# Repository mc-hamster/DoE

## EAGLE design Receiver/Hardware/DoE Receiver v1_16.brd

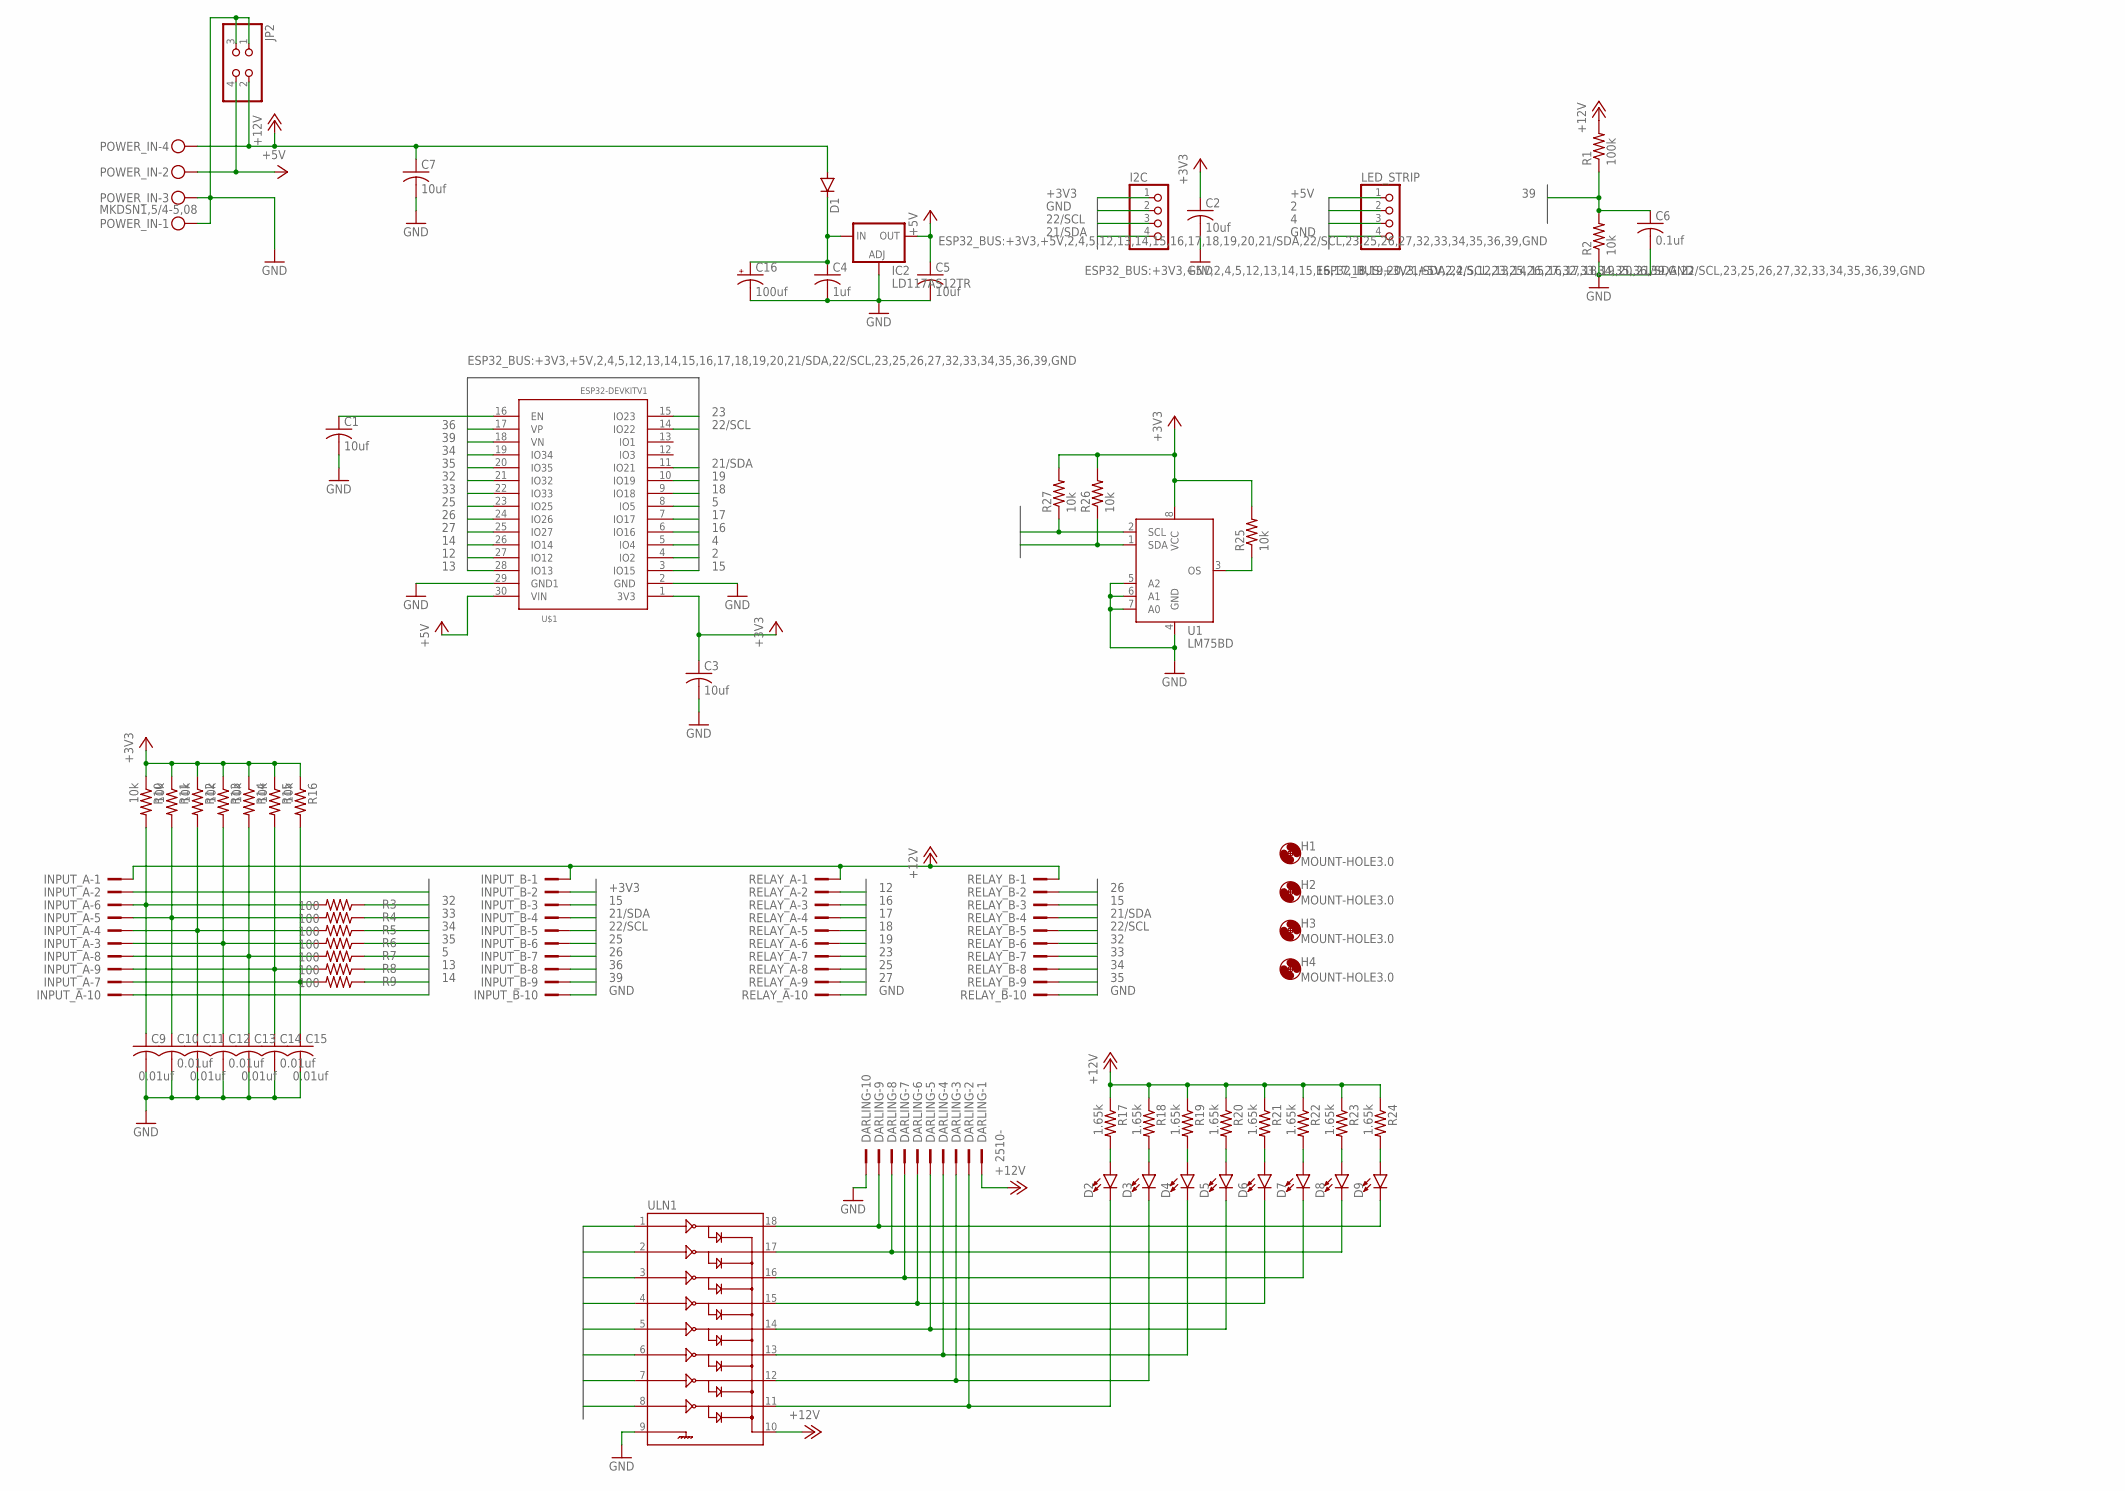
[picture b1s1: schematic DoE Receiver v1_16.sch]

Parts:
C1, C2, C3, C5: 10uf; C0603; LCSC_PART_NUMBER C19702
C4: 1uf; C0805; LCSC_PART_NUMBER C15849
C6: 0.1uf; C0603; LCSC_PART_NUMBER C14663
C7: 10uf; C0805; LCSC_PART_NUMBER C19702
C9, C10, C11, C12, C13, C14, C15: 0.01uf; C0603; LCSC_PART_NUMBER C57112
C16: 100uf; 153CLV-0807; LCSC_PART_NUMBER C249469
D1: DIODE-DO-214AC; DO-214AC; LCSC_PART_NUMBER C95872
D2, D3, D4, D5, D6, D7, D8, D9: LED0603; LED-0603; LCSC_PART_NUMBER C40378
DARLING: 2510-; PAK100/2500-10
H1, H2, H3, H4: MOUNT-HOLE3.0; 3,0
I2C: PINHD-1X4; 1X04
IC2: LD117AS12TR; SOT223; LCSC_PART_NUMBER C6187
INPUT_A: 2510-; PAK100/2500-10
INPUT_B: 2510-; PAK100/2500-10
JP2: PINHD-2X2; 2X02
LED_STRIP: PINHD-1X4/90; 1X04/90
POWER_IN: MKDSN1,5/4-5,08
R1: 100k; R0603; LCSC_PART_NUMBER C25803
R2, R10, R11, R12, R13, R14, R15, R16, R25, R26, R27: 10k; R0603; LCSC_PART_NUMBER C25804
R3, R4, R5, R6, R7, R8, R9: 100; R0603; LCSC_PART_NUMBER C22775
R17, R18, R19, R20, R21, R22, R23, R24: 1.65k; R0603; LCSC_PART_NUMBER C4177
RELAY_A: 2510-; PAK100/2500-10
RELAY_B: 2510-; PAK100/2500-10
U1: LM75BD; SOT96-1; LCSC_PART_NUMBER C34565
U$1: ESP32DEVKITV1; ESP32-DEVKITV1
ULN1: ULN2803SOIC; SO018; LCSC_PART_NUMBER C9683

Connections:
2: LED_STRIP.2, U$1.4 (IO2)
4: LED_STRIP.3, U$1.5 (IO4)
5: R7.1, U$1.8 (IO5)
12: RELAY_A.2, U$1.27 (IO12), ULN1.8
13: R8.1, U$1.28 (IO13)
14: R9.1, U$1.26 (IO14)
15: INPUT_B.3, RELAY_B.3, U$1.3 (IO15)
16: RELAY_A.3, U$1.6 (IO16), ULN1.7
17: RELAY_A.4, U$1.7 (IO17), ULN1.6
18: RELAY_A.5, U$1.9 (IO18), ULN1.5
19: RELAY_A.6, U$1.10 (IO19), ULN1.4
21/SDA: I2C.4, INPUT_B.4, R26.1, RELAY_B.4, U1.1 (SDA), U$1.11 (IO21)
22/SCL: I2C.3, INPUT_B.5, R27.1, RELAY_B.5, U1.2 (SCL), U$1.14 (IO22)
23: RELAY_A.7, U$1.15 (IO23), ULN1.3
25: INPUT_B.6, RELAY_A.8, U$1.23 (IO25), ULN1.2
26: INPUT_B.7, RELAY_B.2, U$1.24 (IO26)
27: RELAY_A.9, U$1.25 (IO27), ULN1.1
32: R3.1, RELAY_B.6, U$1.21 (IO32)
33: R4.1, RELAY_B.7, U$1.22 (IO33)
34: R5.1, RELAY_B.8, U$1.19 (IO34)
35: R6.1, RELAY_B.9, U$1.20 (IO35)
36: INPUT_B.8, U$1.17 (VP)
39: C6.1, INPUT_B.9, R1.1, R2.2, U$1.18 (VN)
+3V3: C2.1, C3.1, I2C.1, INPUT_A.2, INPUT_B.2, R10.1, R11.1, R12.1, R13.1, R14.1, R15.1, R16.1, R25.2, R26.2, R27.2, U1.8 (VCC), U$1.1 (3V3)
+5V: C5.1, IC2.4 (OUT), JP2.4, LED_STRIP.1, POWER_IN.2, U$1.30 (VIN)
+12V: C7.1, D1.A, DARLING.1, INPUT_A.1, INPUT_B.1, JP2.2, POWER_IN.4, R1.2, R17.1, R18.1, R19.1, R20.1, R21.1, R22.1, R23.1, R24.1, RELAY_A.1, RELAY_B.1, ULN1.10
GND: C1.2, C2.2, C3.2, C4.2, C5.2, C6.2, C7.2, C9.2, C10.2, C11.2, C12.2, C13.2, C14.2, C15.2, C16.-, DARLING.10, I2C.2, IC2.1 (ADJ), INPUT_A.10, INPUT_B.10, JP2.1, JP2.3, LED_STRIP.4, POWER_IN.1, POWER_IN.3, R2.1, RELAY_A.10, RELAY_B.10, U1.4 (GND), U1.5 (A2), U1.6 (A1), U1.7 (A0), U$1.2 (GND), U$1.29 (GND1), ULN1.9
unnamed: C1.1, U$1.16 (EN)
unnamed: C4.1, C16.+, D1.C, IC2.3 (IN)
unnamed: C9.1, INPUT_A.6, R3.2, R10.2
unnamed: C10.1, INPUT_A.5, R4.2, R11.2
unnamed: C11.1, INPUT_A.4, R5.2, R12.2
unnamed: C12.1, INPUT_A.3, R6.2, R13.2
unnamed: C13.1, INPUT_A.8, R7.2, R14.2
unnamed: C14.1, INPUT_A.9, R8.2, R15.2
unnamed: C15.1, INPUT_A.7, R9.2, R16.2
unnamed: D9.C, DARLING.9, ULN1.18
unnamed: D8.C, DARLING.8, ULN1.17
unnamed: D7.C, DARLING.7, ULN1.16
unnamed: D6.C, DARLING.6, ULN1.15
unnamed: D5.C, DARLING.5, ULN1.14
unnamed: D4.C, DARLING.4, ULN1.13
unnamed: D3.C, DARLING.3, ULN1.12
unnamed: D2.C, DARLING.2, ULN1.11
unnamed: D2.A, R17.2
unnamed: D3.A, R18.2
unnamed: D4.A, R19.2
unnamed: D5.A, R20.2
unnamed: D6.A, R21.2
unnamed: D7.A, R22.2
unnamed: D8.A, R23.2
unnamed: D9.A, R24.2
unnamed: R25.1, U1.3 (OS)

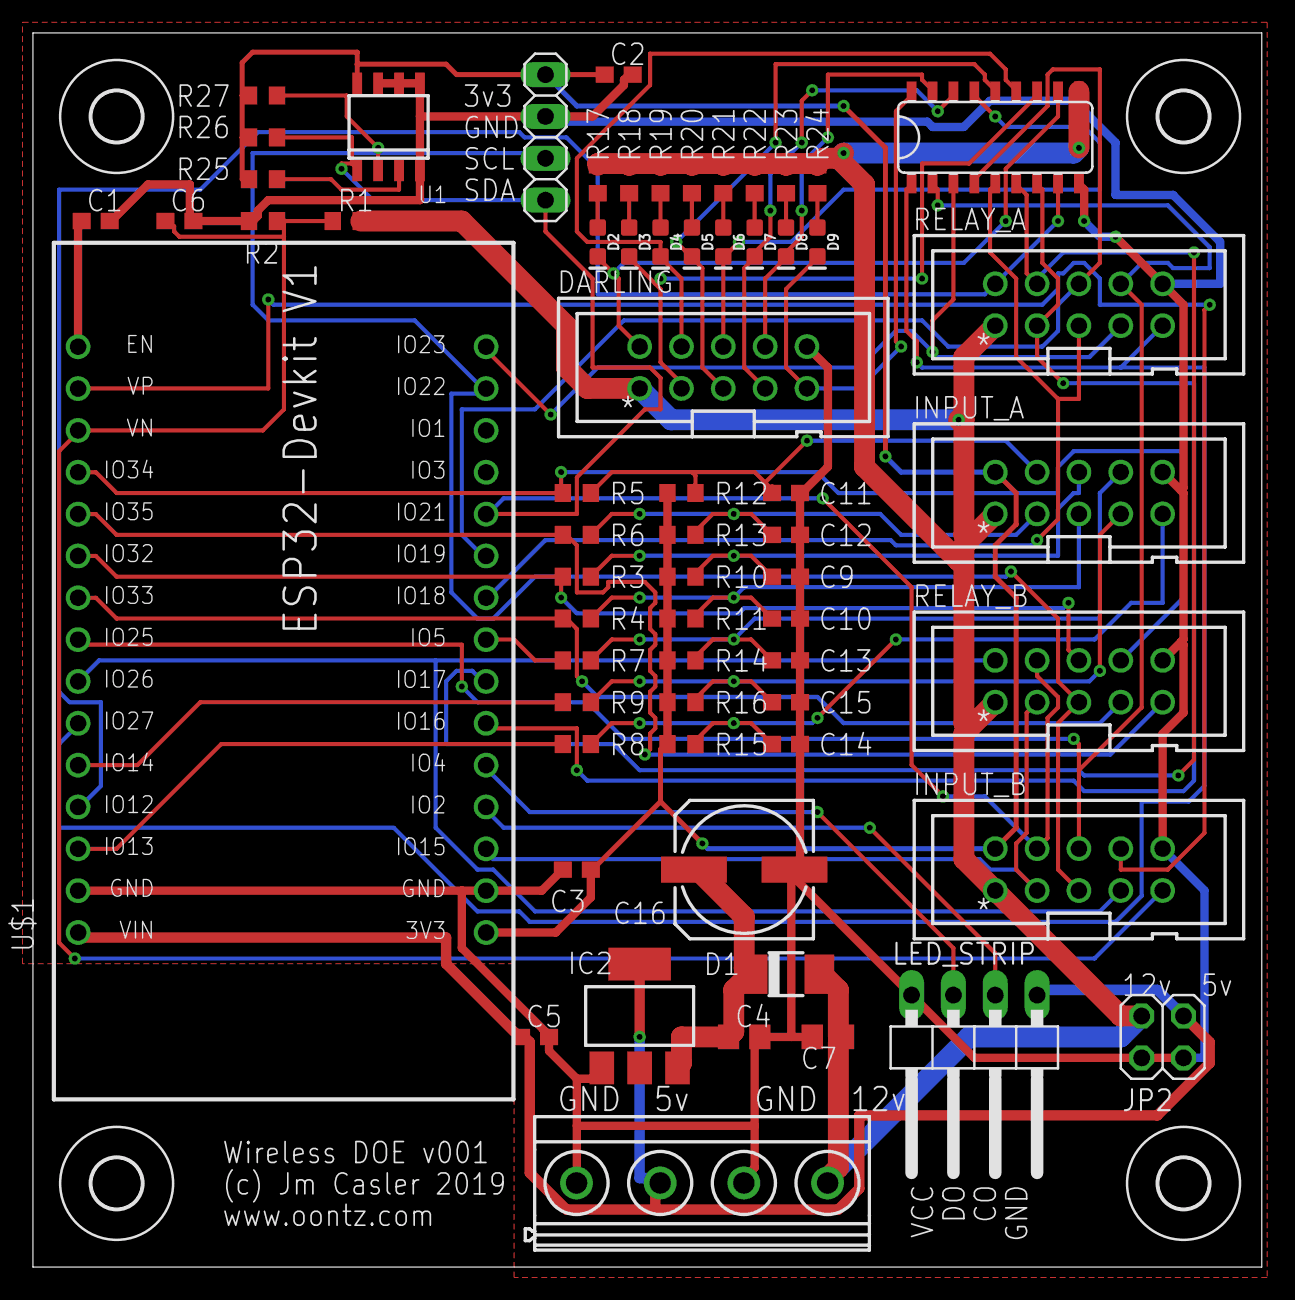
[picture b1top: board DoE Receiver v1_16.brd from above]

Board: 2 copper layers, 74.6 x 74.9 mm, 68 parts (0 on the bottom side), 53 nets.

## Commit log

2020-01-10 Initial Commit of the Receiver Schematic and PCB.
    These have been submitted for manufacture. 30 prototypes will be created from this design.

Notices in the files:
parts and their libraries:
SparkFun-PowerIC: Licensing: CC v3.0 Share-Alike You are welcome to use this library for commercial purposes.
SparkFun-LED: Licensing: Creative Commons ShareAlike 4.0 International - https://creativecommons.org/licenses/by-sa/4.0
